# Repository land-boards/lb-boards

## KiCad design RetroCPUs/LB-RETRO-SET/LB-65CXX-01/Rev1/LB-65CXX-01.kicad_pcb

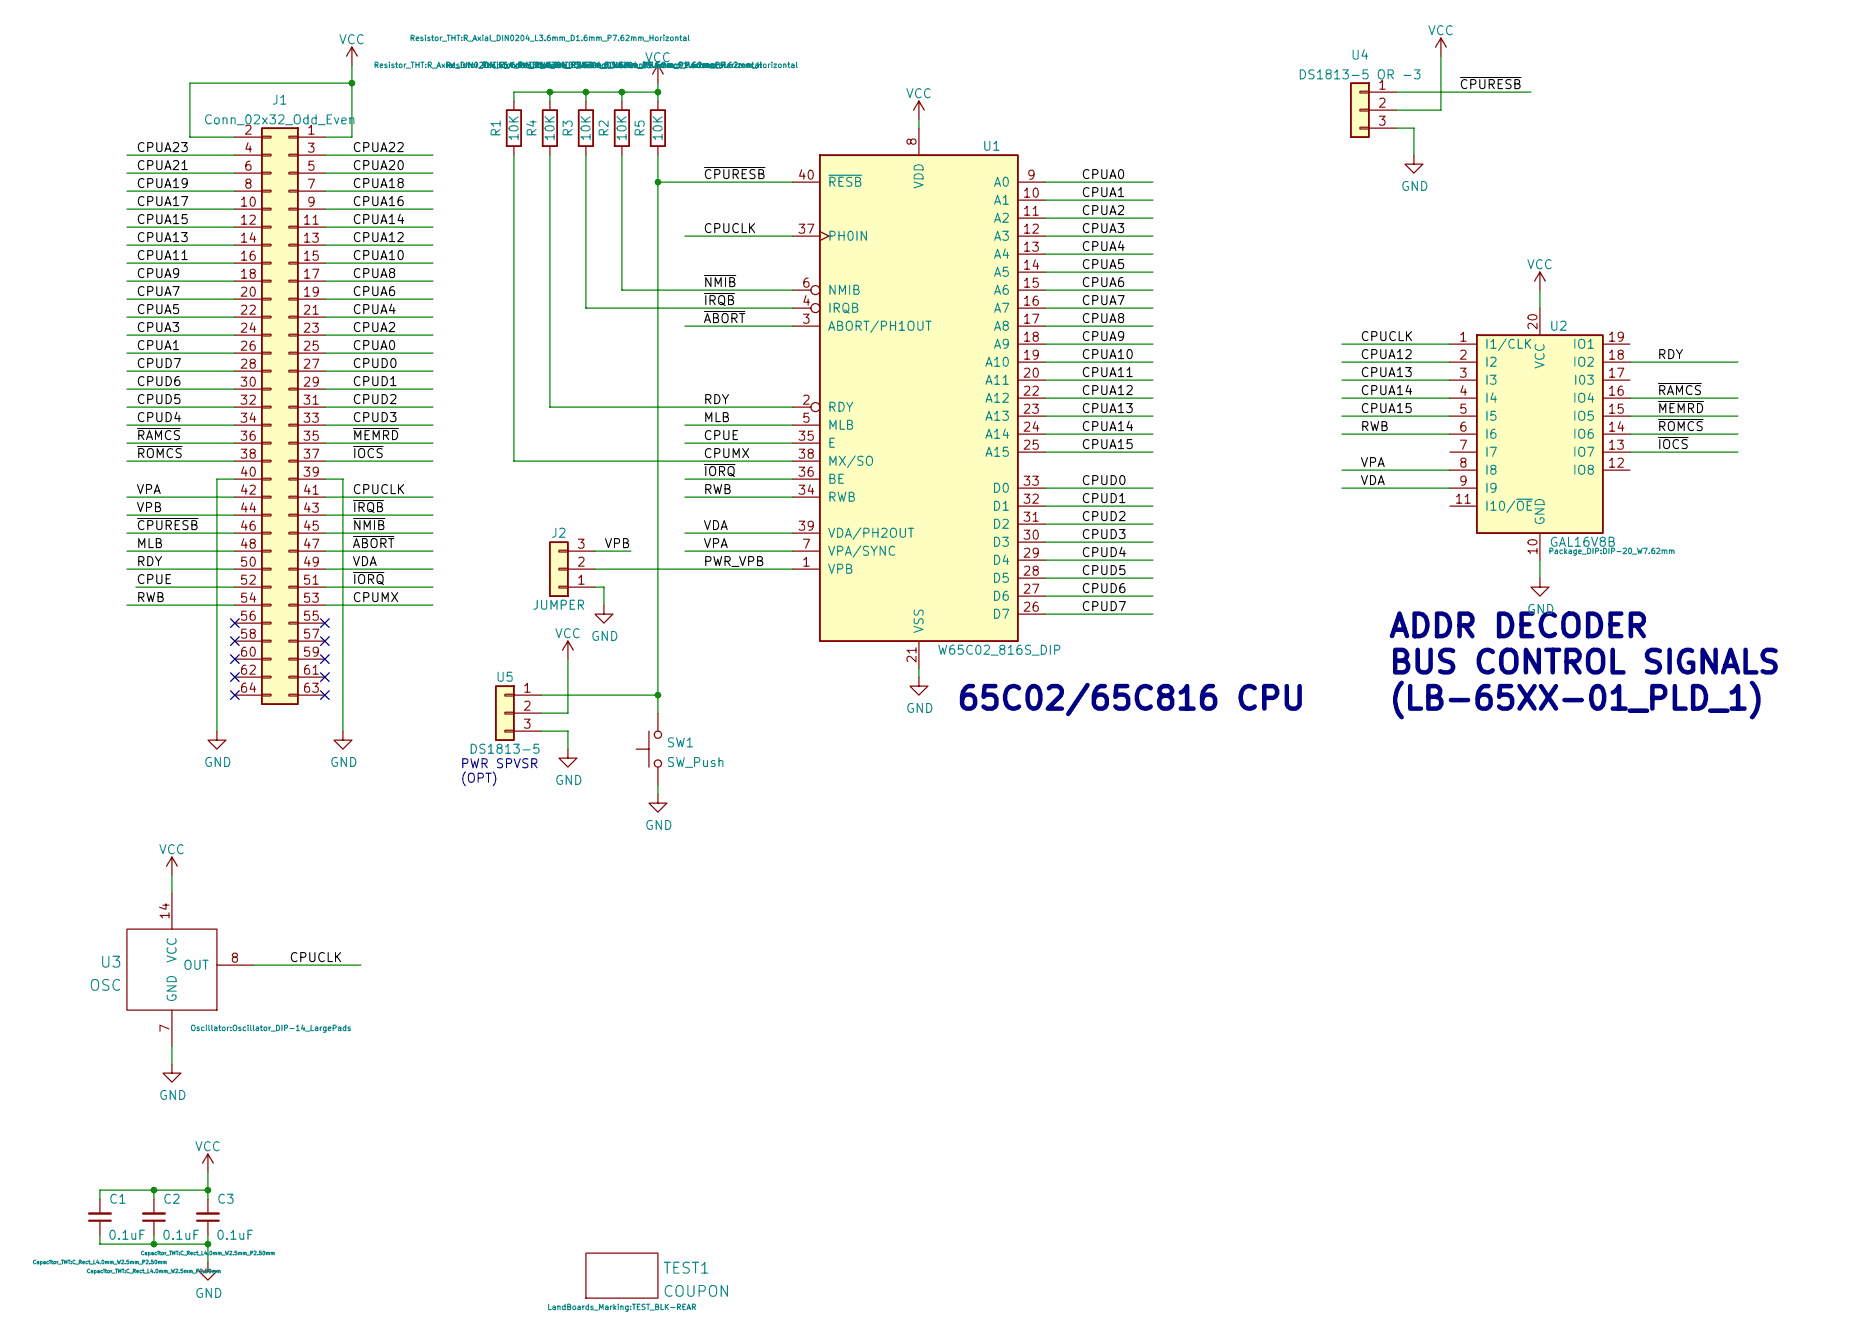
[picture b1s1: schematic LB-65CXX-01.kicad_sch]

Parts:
C1, C2, C3: 0.1uF; C_Rect_L4.0mm_W2.5mm_P2.50mm
J1: Conn_02x32_Odd_Even; PinHeader_2x32_P2.54mm_Horizontal-FLIPPED
J2: JUMPER; PinHeader_1x03_P2.54mm_Vertical
R1, R2, R3, R4, R5: 10K; R_Axial_DIN0204_L3.6mm_D1.6mm_P7.62mm_Horizontal
SW1: SW_Push; SW_PUSH_6mm_H8.5mm
TEST1: COUPON; TEST_BLK-REAR
U1: W65C02_816S_DIP; DIP-40_W15.24mm_LongPads
U2: GAL16V8B; DIP-20_W7.62mm
U3: OSC; Oscillator_DIP-14_LargePads
U4: DS1813-5 OR -3; TO-92
U5: DS1813-5; TO-92

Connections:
/CPUA0: J1.25, U1.9 (A0)
/CPUA1: J1.26, U1.10 (A1)
/CPUA2: J1.23, U1.11 (A2)
/CPUA3: J1.24, U1.12 (A3)
/CPUA4: J1.21, U1.13 (A4)
/CPUA5: J1.22, U1.14 (A5)
/CPUA6: J1.19, U1.15 (A6)
/CPUA7: J1.20, U1.16 (A7)
/CPUA8: J1.17, U1.17 (A8)
/CPUA9: J1.18, U1.18 (A9)
/CPUA10: J1.15, U1.19 (A10)
/CPUA11: J1.16, U1.20 (A11)
/CPUA12: J1.13, U1.22 (A12), U2.2 (I2)
/CPUA13: J1.14, U1.23 (A13), U2.3 (I3)
/CPUA14: J1.11, U1.24 (A14), U2.4 (I4)
/CPUA15: J1.12, U1.25 (A15), U2.5 (I5)
/CPUA16: J1.9
/CPUA17: J1.10
/CPUA18: J1.7
/CPUA19: J1.8
/CPUA20: J1.5
/CPUA21: J1.6
/CPUA22: J1.3
/CPUA23: J1.4
/CPUCLK: J1.41, U1.37 (PH0IN), U2.1 (I1/CLK), U3.8 (OUT)
/CPUD0: J1.27, U1.33 (D0)
/CPUD1: J1.29, U1.32 (D1)
/CPUD2: J1.31, U1.31 (D2)
/CPUD3: J1.33, U1.30 (D3)
/CPUD4: J1.34, U1.29 (D4)
/CPUD5: J1.32, U1.28 (D5)
/CPUD6: J1.30, U1.27 (D6)
/CPUD7: J1.28, U1.26 (D7)
/CPUE: J1.52, U1.35 (E)
/CPUMX: J1.53, R1.2, U1.38 (MX/SO)
/MLB: J1.48, U1.5 (MLB)
/PWR_VPB: J2.2, U1.1 (VPB)
/RDY: J1.50, R4.2, U1.2 (RDY), U2.18 (IO2)
/RWB: J1.54, U1.34 (RWB), U2.6 (I6)
/VDA: J1.49, U1.39 (VDA/PH2OUT), U2.9 (I9)
/VPA: J1.42, U1.7 (VPA/SYNC), U2.8 (I8)
/VPB: J1.44, J2.3
/~ABORT: J1.47, U1.3 (ABORT/PH1OUT)
/~CPURESB: J1.46, R5.2, SW1.2, U1.40 (~RESB), U4.1, U5.1
/~IOCS: J1.37, U2.13 (IO7)
/~IORQ: J1.51, U1.36 (BE)
/~IRQB: J1.43, R3.2, U1.4 (IRQB)
/~MEMRD: J1.35, U2.15 (IO5)
/~NMIB: J1.45, R2.2, U1.6 (NMIB)
/~RAMCS: J1.36, U2.16 (IO4)
/~ROMCS: J1.38, U2.14 (IO6)
GND: C1.1, C2.1, C3.1, J1.39, J1.40, J2.1, SW1.1, U1.21 (VSS), U2.10 (GND), U3.7 (GND), U4.3, U5.3
VCC: C1.2, C2.2, C3.2, J1.1, J1.2, R1.1, R2.1, R3.1, R4.1, R5.1, U1.8 (VDD), U2.20 (VCC), U3.14 (VCC), U4.2, U5.2

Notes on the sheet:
65C02/65C816 CPU
PWR SPVSR (OPT)
ADDR DECODER BUS CONTROL SIGNALS (LB-65XX-01_PLD_1)

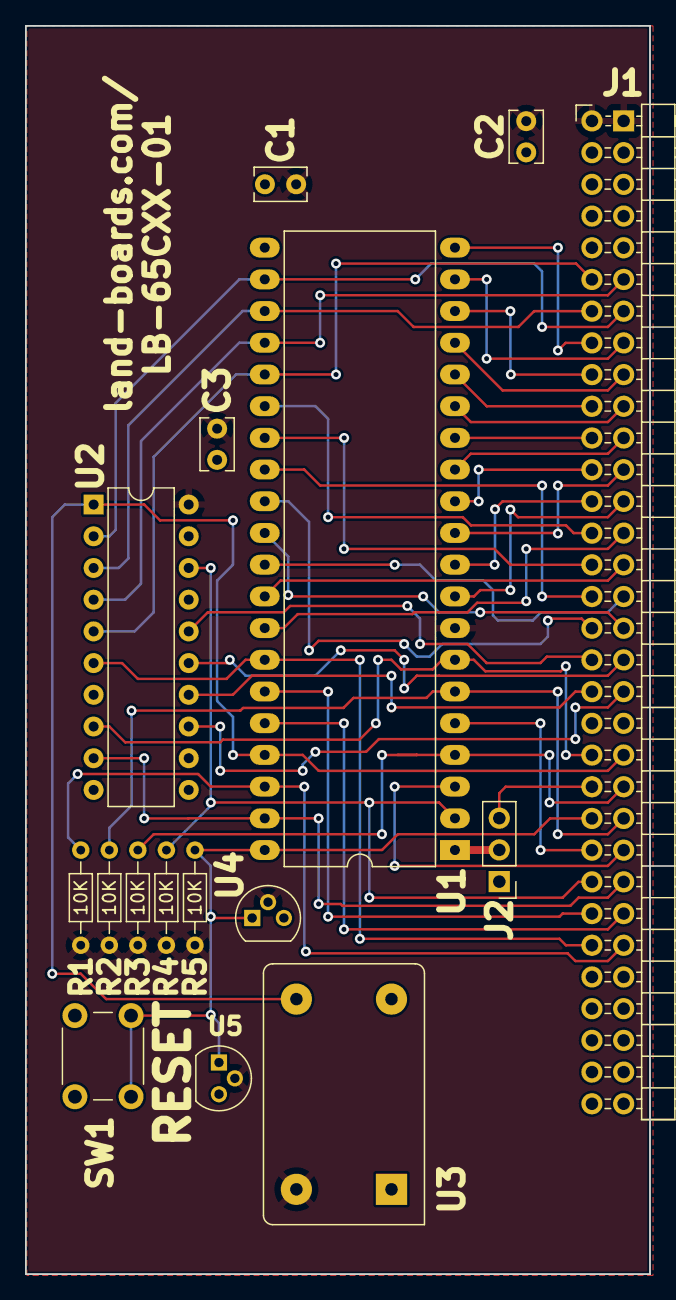
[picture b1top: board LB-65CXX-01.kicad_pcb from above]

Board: 2 copper layers, 50.0 x 100.0 mm, 17 parts (0 on the bottom side), 45 nets.

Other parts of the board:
TEST: COUPON; TEST_BLK-REAR

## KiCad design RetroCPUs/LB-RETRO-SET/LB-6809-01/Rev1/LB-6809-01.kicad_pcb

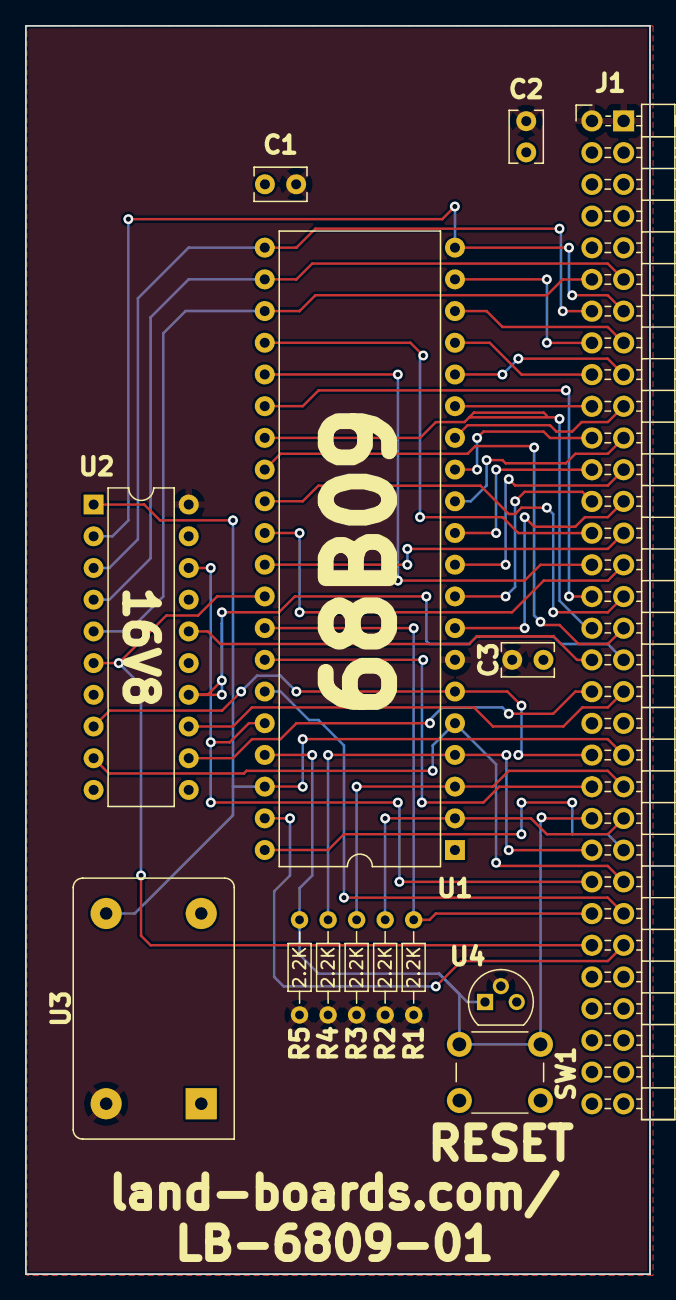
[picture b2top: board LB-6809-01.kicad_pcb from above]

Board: 2 copper layers, 50.0 x 100.0 mm, 15 parts (0 on the bottom side), 44 nets.

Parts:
C1, C2, C3: 0.1uF; C_Rect_L4.0mm_W2.5mm_P2.50mm
J1: Conn_02x32_Odd_Even; PinHeader_2x32_P2.54mm_Horizontal-FLIPPED
R1, R2, R3, R4, R5: 2.2K; R_Axial_DIN0204_L3.6mm_D1.6mm_P7.62mm_Horizontal
SW1: SW_Push; SW_PUSH_6mm_H8.5mm
TEST: COUPON; TEST_BLK-REAR
U1: MC68B09; DIP-40_W15.24mm
U2: GAL16V8; DIP-20_W7.62mm
U3: OSC; Oscillator_DIP-14_LargePads
U4: DS1813-5; TO-92

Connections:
/CPUA0: J1.25, U1.8 (A0)
/CPUA1: J1.26, U1.9 (A1)
/CPUA2: J1.23, U1.10 (A2)
/CPUA3: J1.24, U1.11 (A3)
/CPUA4: J1.21, U1.12 (A4)
/CPUA5: J1.22, U1.13 (A5)
/CPUA6: J1.19, U1.14 (A6)
/CPUA7: J1.20, U1.15 (A7)
/CPUA8: J1.17, U1.16 (A8)
/CPUA9: J1.18, U1.17 (A9)
/CPUA10: J1.15, U1.18 (A10)
/CPUA11: J1.16, U1.19 (A11)
/CPUA12: J1.13, U1.20 (A12), U2.2 (I2)
/CPUA13: J1.14, U1.21 (A13), U2.3 (I3)
/CPUA14: J1.11, U1.22 (A14), U2.4 (I4)
/CPUA15: J1.12, U1.23 (A15), U2.5 (I5)
/CPUCLK: J1.41, U1.38 (EXTAL), U2.1 (I1/CLK), U3.8 (OUT)
/CPUD0: J1.27, U1.31 (D0)
/CPUD1: J1.29, U1.30 (D1)
/CPUD2: J1.31, U1.29 (D2)
/CPUD3: J1.33, U1.28 (D3)
/CPUD4: J1.34, U1.27 (D4)
/CPUD5: J1.32, U1.26 (D5)
/CPUD6: J1.30, U1.25 (D6)
/CPUD7: J1.28, U1.24 (D7)
/CPUE: J1.52, R1.2, U1.33 (~DMA/BREQ)
/CPUMX: J1.53, U1.39 (XTAL)
/MLB: J1.48, R4.2, U1.4 (~FIRQ)
/RDY: J1.50, U1.36 (MRDY), U2.18 (IO2)
/RWB: J1.54, U1.32 (R/~W), U2.6 (I6)
/VDA: J1.49, U1.5 (BS), U2.9 (I9)
/VPA: J1.42, U1.6 (BA), U2.8 (I8)
/VPB: J1.44, U1.34 (E)
/~ABORT: J1.47, U1.40 (~HALT)
/~CPURESB: J1.46, R5.2, SW1.2, U1.37 (~RESET), U4.1
/~IOCS: J1.37, U2.13 (IO7)
/~IORQ: J1.51, U1.35 (Q)
/~IRQB: J1.43, R3.2, U1.3 (~IRQ)
/~MEMRD: J1.35, U2.14 (IO6)
/~NMIB: J1.45, R2.2, U1.2 (~NMI)
/~RAMCS: J1.36, U2.16 (IO4)
/~ROMCS: J1.38, U2.12 (IO8)
GND: C1.1, C2.1, C3.1, J1.39, J1.40, SW1.1, U1.1 (VSS), U2.10 (GND), U3.7 (GND), U4.3
VCC: C1.2, C2.2, C3.2, J1.1, J1.2, R1.1, R2.1, R3.1, R4.1, R5.1, U1.7 (VCC), U2.20 (VCC), U3.14 (VCC), U4.2

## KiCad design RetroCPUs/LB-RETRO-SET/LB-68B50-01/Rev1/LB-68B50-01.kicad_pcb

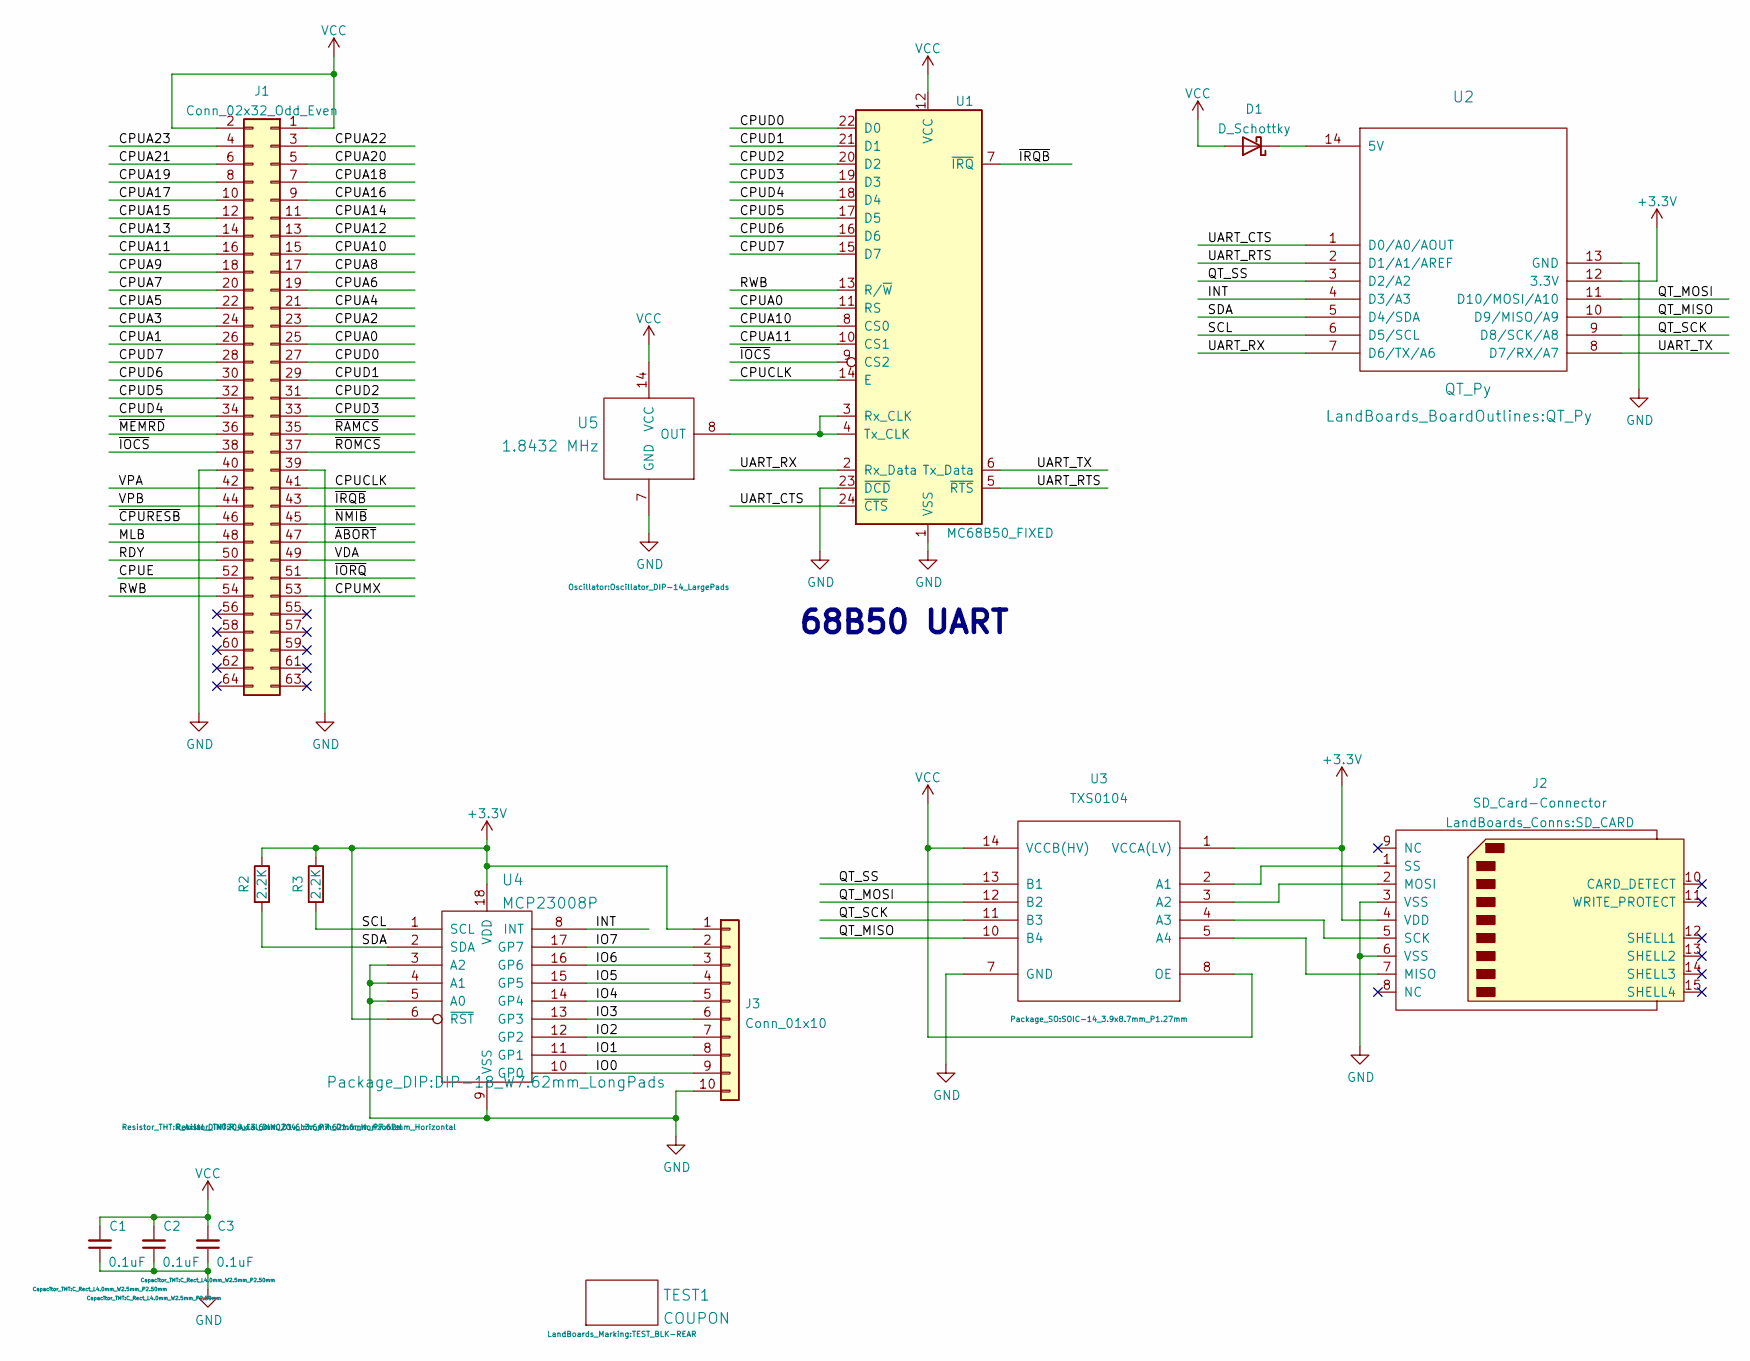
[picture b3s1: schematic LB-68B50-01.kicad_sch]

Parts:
C1, C2, C3: 0.1uF; C_Rect_L4.0mm_W2.5mm_P2.50mm
D1: D_Schottky; D_DO-35_SOD27_P10.16mm_Horizontal
J1: Conn_02x32_Odd_Even; PinHeader_2x32_P2.54mm_Horizontal-FLIPPED
J2: SD_Card-Connector; SD_CARD
J3: Conn_01x10; PinHeader_1x10_P2.54mm_Horizontal
R2, R3: 2.2K; R_Axial_DIN0204_L3.6mm_D1.6mm_P7.62mm_Horizontal
TEST1: COUPON; TEST_BLK-REAR
U1: MC68B50_FIXED; DIP-24_W15.24mm_LongPads
U2: QT_Py
U3: TXS0104; SOIC-14_3.9x8.7mm_P1.27mm
U4: MCP23008P; DIP-18_W7.62mm_LongPads
U5: 1.8432 MHz; Oscillator_DIP-14_LargePads

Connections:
+3V3: J2.4 (VDD), J3.1, R2.1, R3.1, U2.12 (3.3V), U3.1 (VCCA(LV)), U4.6 (~RST), U4.18 (VDD)
/CPUA0: J1.25, U1.11 (RS)
/CPUA1: J1.26
/CPUA2: J1.23
/CPUA3: J1.24
/CPUA4: J1.21
/CPUA5: J1.22
/CPUA6: J1.19
/CPUA7: J1.20
/CPUA8: J1.17
/CPUA9: J1.18
/CPUA10: J1.15, U1.8 (CS0)
/CPUA11: J1.16, U1.10 (CS1)
/CPUA12: J1.13
/CPUA13: J1.14
/CPUA14: J1.11
/CPUA15: J1.12
/CPUA16: J1.9
/CPUA17: J1.10
/CPUA18: J1.7
/CPUA19: J1.8
/CPUA20: J1.5
/CPUA21: J1.6
/CPUA22: J1.3
/CPUA23: J1.4
/CPUCLK: J1.41, U1.14 (E)
/CPUD0: J1.27, U1.22 (D0)
/CPUD1: J1.29, U1.21 (D1)
/CPUD2: J1.31, U1.20 (D2)
/CPUD3: J1.33, U1.19 (D3)
/CPUD4: J1.34, U1.18 (D4)
/CPUD5: J1.32, U1.17 (D5)
/CPUD6: J1.30, U1.16 (D6)
/CPUD7: J1.28, U1.15 (D7)
/CPUE: J1.52
/CPUMX: J1.53
/INT: U2.4 (D3/A3), U4.8 (INT)
/IO0: J3.9, U4.10 (GP0)
/IO1: J3.8, U4.11 (GP1)
/IO2: J3.7, U4.12 (GP2)
/IO3: J3.6, U4.13 (GP3)
/IO4: J3.5, U4.14 (GP4)
/IO5: J3.4, U4.15 (GP5)
/IO6: J3.3, U4.16 (GP6)
/IO7: J3.2, U4.17 (GP7)
/MLB: J1.48
/QT_MISO: U2.10 (D9/MISO/A9), U3.10 (B4)
/QT_MOSI: U2.11 (D10/MOSI/A10), U3.12 (B2)
/QT_SCK: U2.9 (D8/SCK/A8), U3.11 (B3)
/QT_SS: U2.3 (D2/A2), U3.13 (B1)
/RDY: J1.50
/RWB: J1.54, U1.13 (R/~W)
/SCL: R3.2, U2.6 (D5/SCL), U4.1 (SCL)
/SDA: R2.2, U2.5 (D4/SDA), U4.2 (SDA)
/UART_CTS: U1.24 (~CTS), U2.1 (D0/A0/AOUT)
/UART_RTS: U1.5 (~RTS), U2.2 (D1/A1/AREF)
/UART_RX: U1.2 (Rx_Data), U2.7 (D6/TX/A6)
/UART_TX: U1.6 (Tx_Data), U2.8 (D7/RX/A7)
/VDA: J1.49
/VPA: J1.42
/VPB: J1.44
/~ABORT: J1.47
/~CPURESB: J1.46
/~IOCS: J1.38, U1.9 (CS2)
/~IORQ: J1.51
/~IRQB: J1.43, U1.7 (~IRQ)
/~MEMRD: J1.36
/~NMIB: J1.45
/~RAMCS: J1.35
/~ROMCS: J1.37
GND: C1.1, C2.1, C3.1, J1.39, J1.40, J2.3 (VSS), J2.6 (VSS), J3.10, U1.1 (VSS), U1.23 (~DCD), U2.13 (GND), U3.7 (GND), U4.3 (A2), U4.4 (A1), U4.5 (A0), U4.9 (VSS), U5.7 (GND)
unnamed: J2.1 (SS), U3.2 (A1)
unnamed: J2.2 (MOSI), U3.3 (A2)
unnamed: J2.5 (SCK), U3.4 (A3)
unnamed: J2.7 (MISO), U3.5 (A4)
unnamed: U1.3 (Rx_CLK), U1.4 (Tx_CLK), U5.8 (OUT)
unnamed: D1.1 (K), U2.14 (5V)
VCC: C1.2, C2.2, C3.2, D1.2 (A), J1.1, J1.2, U1.12 (VCC), U3.8 (OE), U3.14 (VCCB(HV)), U5.14 (VCC)

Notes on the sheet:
68B50 UART

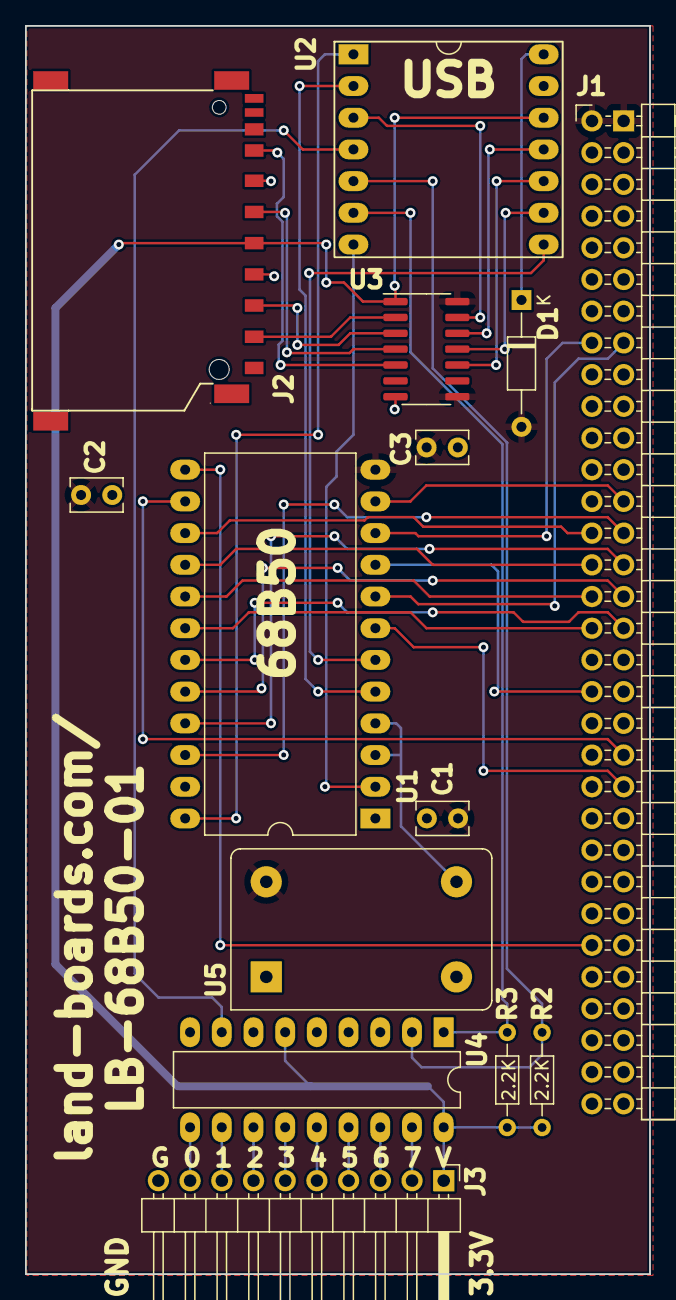
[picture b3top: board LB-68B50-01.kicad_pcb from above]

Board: 2 copper layers, 50.0 x 100.0 mm, 15 parts (0 on the bottom side), 43 nets.

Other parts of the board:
TEST: COUPON; TEST_BLK-REAR

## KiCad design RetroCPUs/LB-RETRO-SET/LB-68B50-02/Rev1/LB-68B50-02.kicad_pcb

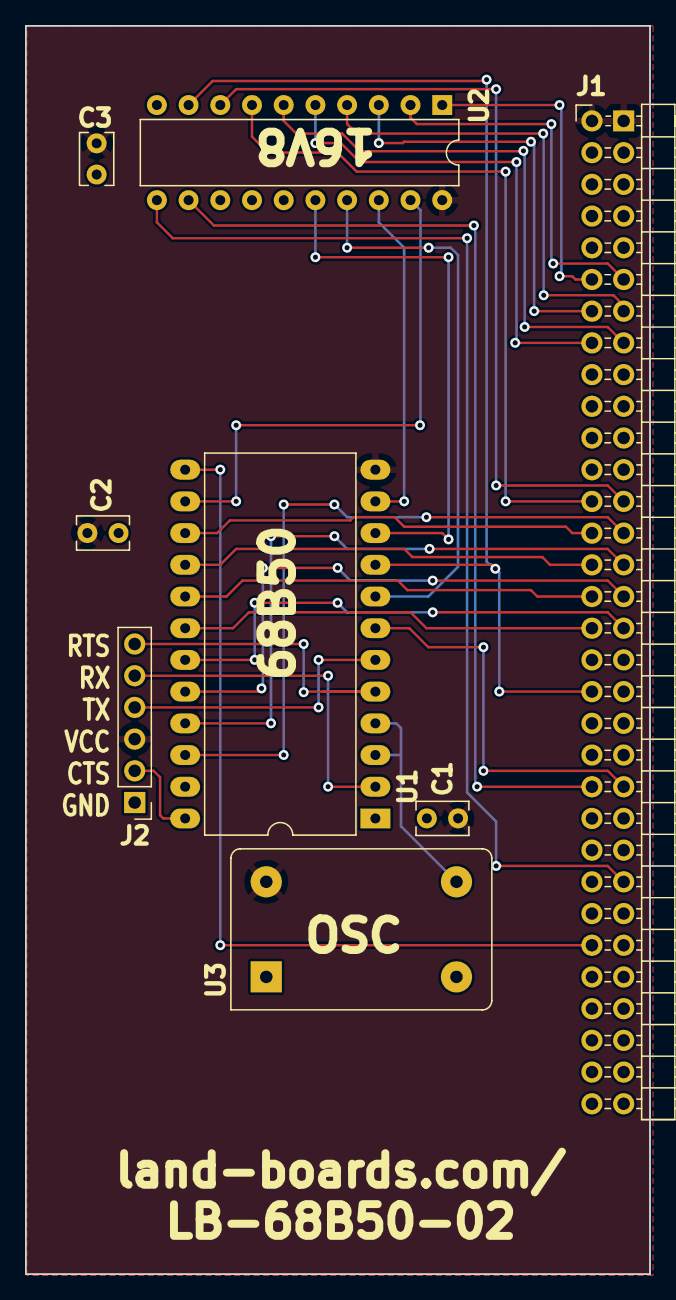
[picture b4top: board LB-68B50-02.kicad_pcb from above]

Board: 2 copper layers, 50.0 x 100.0 mm, 9 parts (0 on the bottom side), 32 nets.

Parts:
C1, C2, C3: 0.1uF; C_Rect_L4.0mm_W2.5mm_P2.50mm
J1: Conn_2x32_RtAng; PinHeader_2x32_P2.54mm_Horizontal-FLIPPED
J2: 1x6_Pin_Header_Rt_Angle; PinHeader_1x06_P2.54mm_Vertical
TEST: COUPON; TEST_BLK-REAR
U1: MC68B50; DIP-24_W15.24mm_LongPads
U2: ATF16V8B-15PU; DIP-20_W7.62mm
U3: MXO45-3C-1M8432; Oscillator_DIP-14_LargePads

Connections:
/ACIACS0: U1.8 (CS0), U2.17 (I03)
/ACIACS1: U1.10 (CS1), U2.16 (IO4)
/ACIAE: U1.14 (E), U2.19 (IO1)
/ACIARS: U1.11 (RS), U2.18 (IO2)
/CPUA0: J1.25, U2.8 (I8)
/CPUA1: J1.26, U2.7 (I7)
/CPUA10: J1.15, U2.6 (I6)
/CPUA11: J1.16, U2.5 (I5)
/CPUA12: J1.13, U2.4 (I4)
/CPUA13: J1.14, U2.3 (I3)
/CPUA14: J1.11, U2.2 (I2)
/CPUA15: J1.12, U2.1 (I1/CLK)
/CPUD0: J1.27, U1.22 (D0)
/CPUD1: J1.29, U1.21 (D1)
/CPUD2: J1.31, U1.20 (D2)
/CPUD3: J1.33, U1.19 (D3)
/CPUD4: J1.34, U1.18 (D4)
/CPUD5: J1.32, U1.17 (D5)
/CPUD6: J1.30, U1.16 (D6)
/CPUD7: J1.28, U1.15 (D7)
/RWB: J1.54, U1.13 (R/~W)
/UART_CTS_5: J2.2 (<CTS), U1.24 (~CTS)
/UART_RTS_5: J2.6 (RTS>), U1.5 (~RTS)
/UART_RX_5: J2.5 (RX<), U1.2 (Rx_Data)
/UART_TX_5: J2.4 (TX>), U1.6 (Tx_Data)
/VDA: J1.49, U2.11 (I10/~OE)
/VPB: J1.44, U2.12 (IO8)
/~IOCS: J1.38, U1.9 (CS2), U2.9 (I9)
/~IRQB: J1.43, U1.7 (~IRQ)
GND: C1.1, C2.1, C3.1, J1.39, J1.40, J2.1 (GND), U1.1 (VSS), U1.23 (~DCD), U2.10 (GND), U3.7 (GND)
unnamed: U1.3 (Rx_CLK), U1.4 (Tx_CLK), U3.8 (OUT)
VCC: C1.2, C2.2, C3.2, J1.1, J1.2, J2.3 (VCC), U1.12 (VCC), U2.20 (VCC), U3.14 (VCC)

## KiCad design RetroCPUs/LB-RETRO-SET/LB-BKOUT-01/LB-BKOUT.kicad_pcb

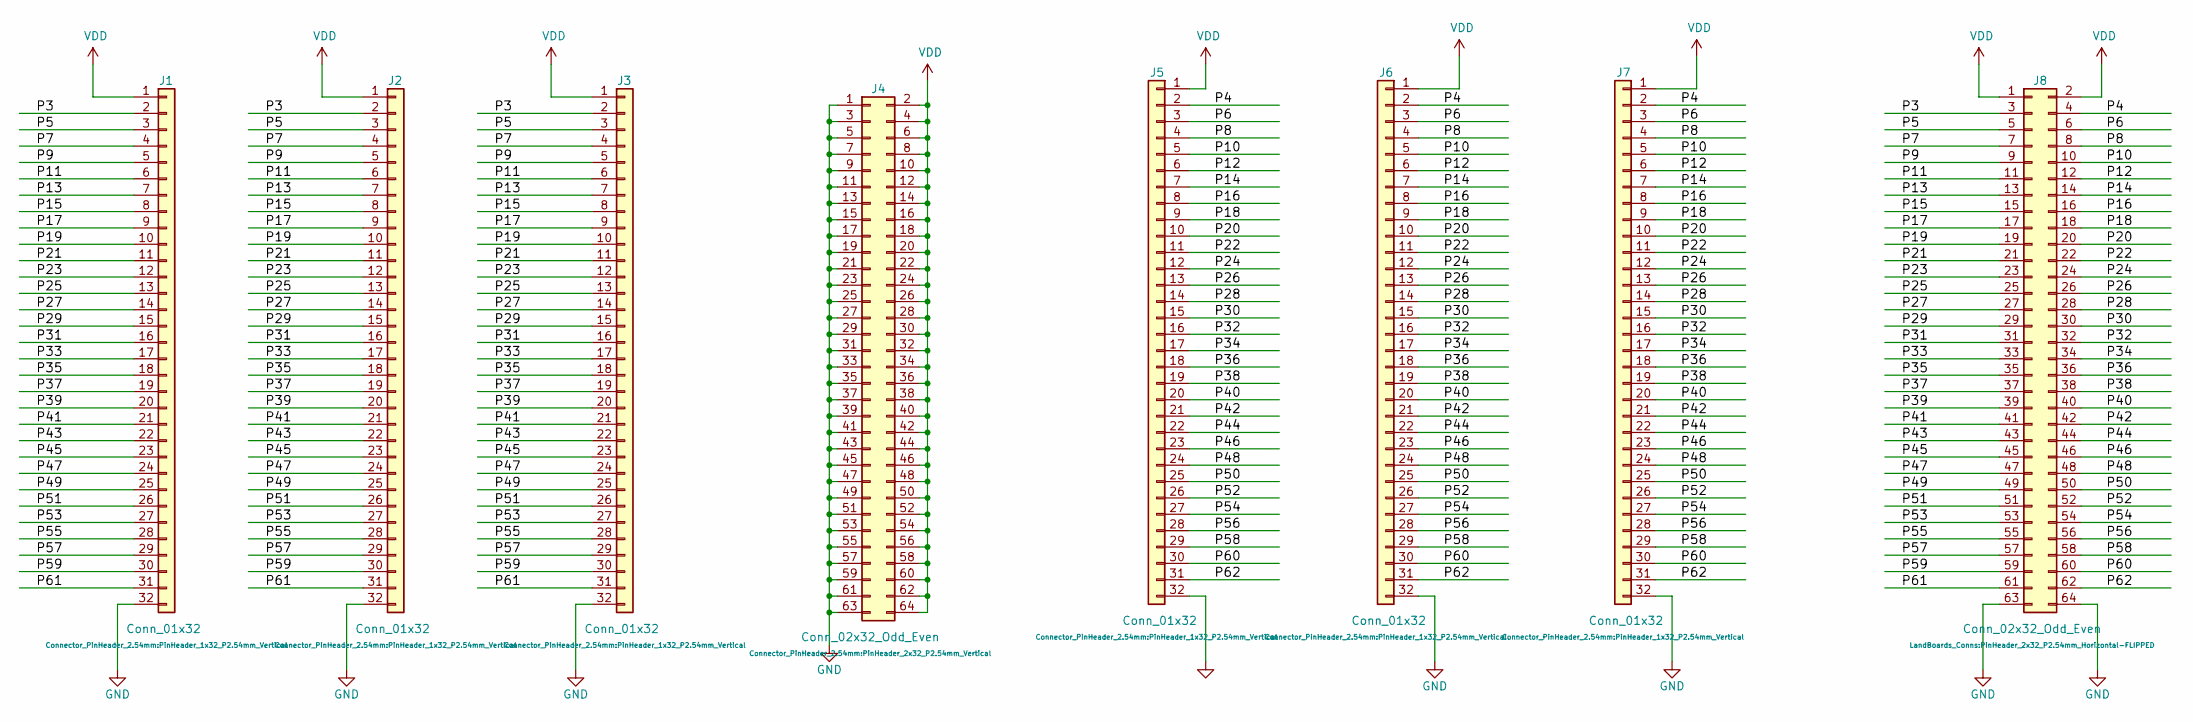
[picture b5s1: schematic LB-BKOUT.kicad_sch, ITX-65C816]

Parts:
J1, J2, J3, J5, J6, J7: Conn_01x32; PinHeader_1x32_P2.54mm_Vertical
J4: Conn_02x32_Odd_Even; PinHeader_2x32_P2.54mm_Vertical
J8: Conn_02x32_Odd_Even; PinHeader_2x32_P2.54mm_Horizontal-FLIPPED

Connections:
/P3: J1.2, J2.2, J3.2, J8.3
/P4: J5.2, J6.2, J7.2, J8.4
/P5: J1.3, J2.3, J3.3, J8.5
/P6: J5.3, J6.3, J7.3, J8.6
/P7: J1.4, J2.4, J3.4, J8.7
/P8: J5.4, J6.4, J7.4, J8.8
/P9: J1.5, J2.5, J3.5, J8.9
/P10: J5.5, J6.5, J7.5, J8.10
/P11: J1.6, J2.6, J3.6, J8.11
/P12: J5.6, J6.6, J7.6, J8.12
/P13: J1.7, J2.7, J3.7, J8.13
/P14: J5.7, J6.7, J7.7, J8.14
/P15: J1.8, J2.8, J3.8, J8.15
/P16: J5.8, J6.8, J7.8, J8.16
/P17: J1.9, J2.9, J3.9, J8.17
/P18: J5.9, J6.9, J7.9, J8.18
/P19: J1.10, J2.10, J3.10, J8.19
/P20: J5.10, J6.10, J7.10, J8.20
/P21: J1.11, J2.11, J3.11, J8.21
/P22: J5.11, J6.11, J7.11, J8.22
/P23: J1.12, J2.12, J3.12, J8.23
/P24: J5.12, J6.12, J7.12, J8.24
/P25: J1.13, J2.13, J3.13, J8.25
/P26: J5.13, J6.13, J7.13, J8.26
/P27: J1.14, J2.14, J3.14, J8.27
/P28: J5.14, J6.14, J7.14, J8.28
/P29: J1.15, J2.15, J3.15, J8.29
/P30: J5.15, J6.15, J7.15, J8.30
/P31: J1.16, J2.16, J3.16, J8.31
/P32: J5.16, J6.16, J7.16, J8.32
/P33: J1.17, J2.17, J3.17, J8.33
/P34: J5.17, J6.17, J7.17, J8.34
/P35: J1.18, J2.18, J3.18, J8.35
/P36: J5.18, J6.18, J7.18, J8.36
/P37: J1.19, J2.19, J3.19, J8.37
/P38: J5.19, J6.19, J7.19, J8.38
/P39: J1.20, J2.20, J3.20, J8.39
/P40: J5.20, J6.20, J7.20, J8.40
/P41: J1.21, J2.21, J3.21, J8.41
/P42: J5.21, J6.21, J7.21, J8.42
/P43: J1.22, J2.22, J3.22, J8.43
/P44: J5.22, J6.22, J7.22, J8.44
/P45: J1.23, J2.23, J3.23, J8.45
/P46: J5.23, J6.23, J7.23, J8.46
/P47: J1.24, J2.24, J3.24, J8.47
/P48: J5.24, J6.24, J7.24, J8.48
/P49: J1.25, J2.25, J3.25, J8.49
/P50: J5.25, J6.25, J7.25, J8.50
/P51: J1.26, J2.26, J3.26, J8.51
/P52: J5.26, J6.26, J7.26, J8.52
/P53: J1.27, J2.27, J3.27, J8.53
/P54: J5.27, J6.27, J7.27, J8.54
/P55: J1.28, J2.28, J3.28, J8.55
/P56: J5.28, J6.28, J7.28, J8.56
/P57: J1.29, J2.29, J3.29, J8.57
/P58: J5.29, J6.29, J7.29, J8.58
/P59: J1.30, J2.30, J3.30, J8.59
/P60: J5.30, J6.30, J7.30, J8.60
/P61: J1.31, J2.31, J3.31, J8.61
/P62: J5.31, J6.31, J7.31, J8.62
GND: J1.32, J2.32, J3.32, J4.1, J4.3, J4.5, J4.7, J4.9, J4.11, J4.13, J4.15, J4.17, J4.19, J4.21, J4.23, J4.25, J4.27, J4.29, J4.31, J4.33, J4.35, J4.37, J4.39, J4.41, J4.43, J4.45, J4.47, J4.49, J4.51, J4.53, J4.55, J4.57, J4.59, J4.61, J4.63, J5.32, J6.32, J7.32, J8.63, J8.64
VDD: J1.1, J2.1, J3.1, J4.2, J4.4, J4.6, J4.8, J4.10, J4.12, J4.14, J4.16, J4.18, J4.20, J4.22, J4.24, J4.26, J4.28, J4.30, J4.32, J4.34, J4.36, J4.38, J4.40, J4.42, J4.44, J4.46, J4.48, J4.50, J4.52, J4.54, J4.56, J4.58, J4.60, J4.62, J4.64, J5.1, J6.1, J7.1, J8.1, J8.2

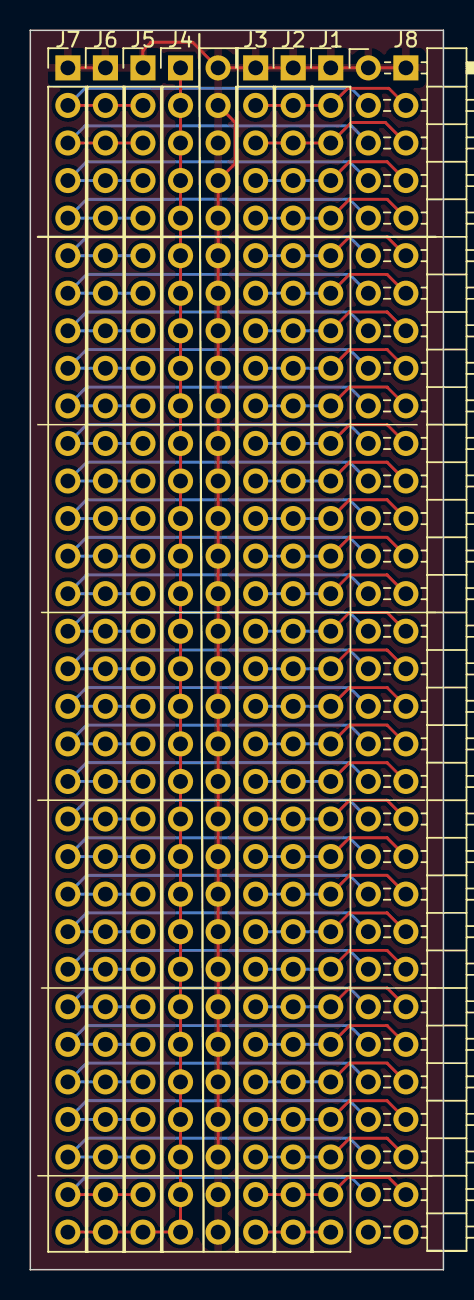
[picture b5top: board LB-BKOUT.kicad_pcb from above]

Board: 2 copper layers, 27.9 x 83.8 mm, 8 parts (0 on the bottom side), 62 nets.

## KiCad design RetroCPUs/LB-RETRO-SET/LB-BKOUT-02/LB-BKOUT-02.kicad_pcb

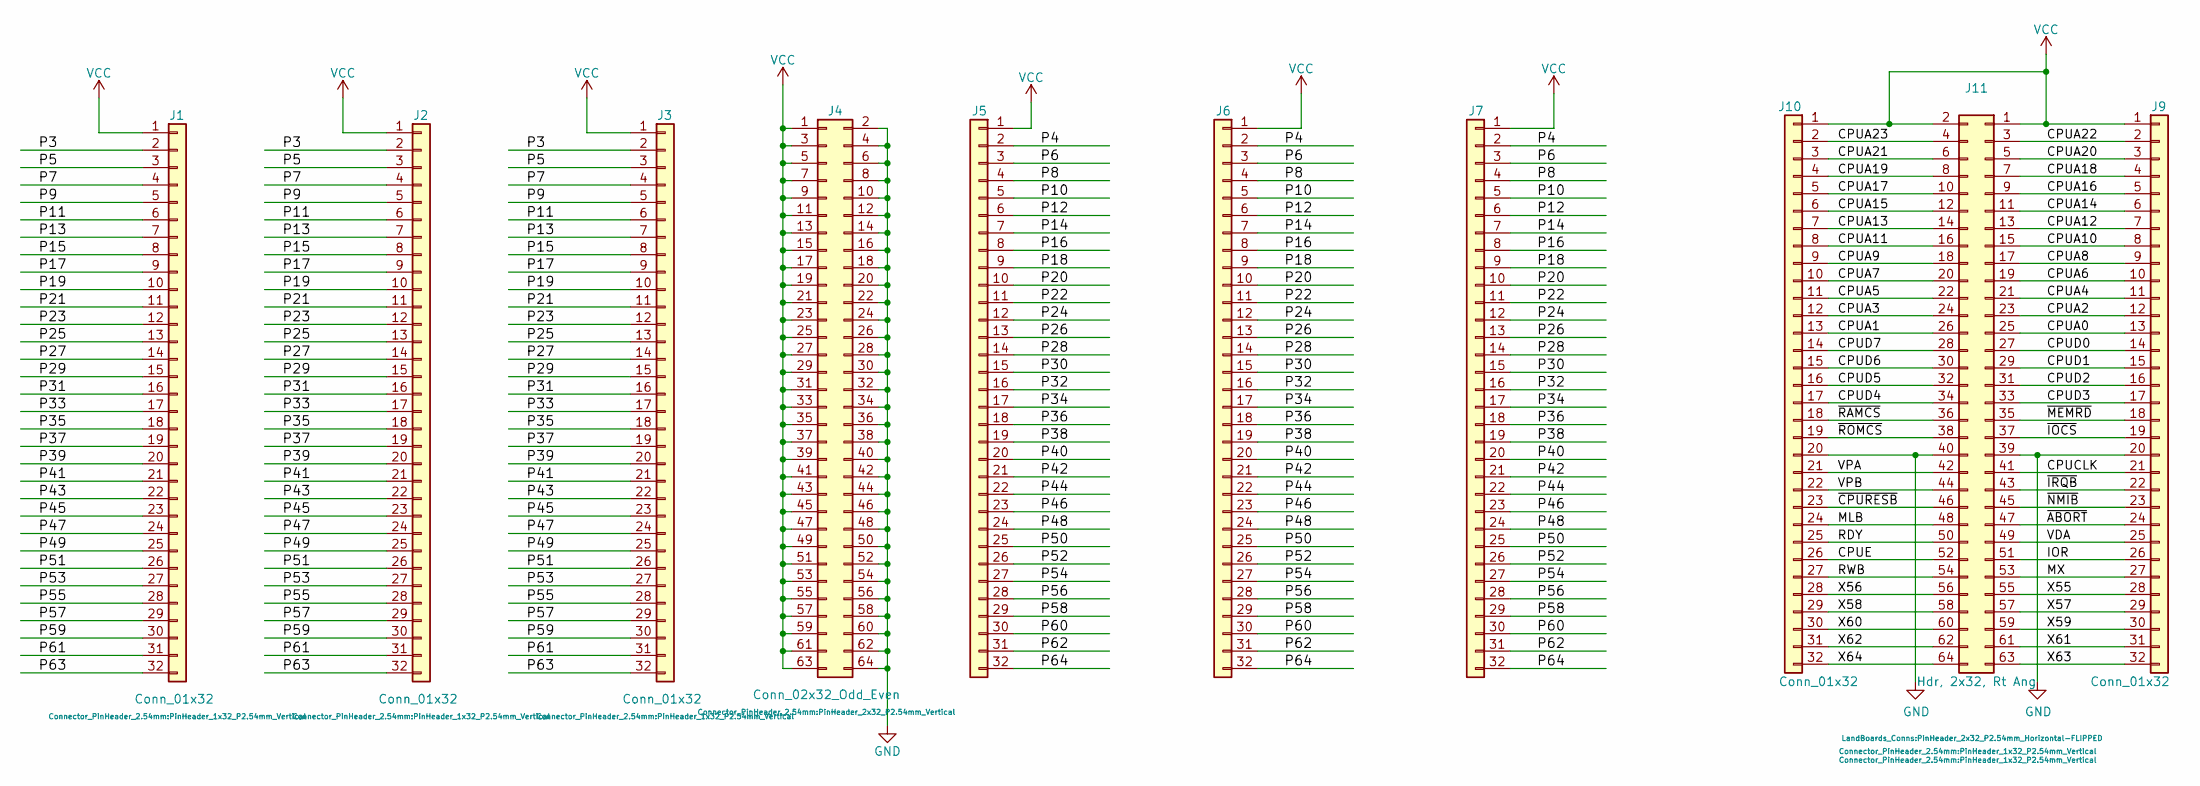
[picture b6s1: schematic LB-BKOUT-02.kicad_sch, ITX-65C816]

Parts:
J1, J2, J3, J5, J6, J7, J9, J10: Conn_01x32; PinHeader_1x32_P2.54mm_Vertical
J4: Conn_02x32_Odd_Even; PinHeader_2x32_P2.54mm_Vertical
J11: Hdr, 2x32, Rt Ang; PinHeader_2x32_P2.54mm_Horizontal-FLIPPED

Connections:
/CPUA0: J9.13, J11.25
/CPUA1: J10.13, J11.26
/CPUA2: J9.12, J11.23
/CPUA3: J10.12, J11.24
/CPUA4: J9.11, J11.21
/CPUA5: J10.11, J11.22
/CPUA6: J9.10, J11.19
/CPUA7: J10.10, J11.20
/CPUA8: J9.9, J11.17
/CPUA9: J10.9, J11.18
/CPUA10: J9.8, J11.15
/CPUA11: J10.8, J11.16
/CPUA12: J9.7, J11.13
/CPUA13: J10.7, J11.14
/CPUA14: J9.6, J11.11
/CPUA15: J10.6, J11.12
/CPUA16: J9.5, J11.9
/CPUA17: J10.5, J11.10
/CPUA18: J9.4, J11.7
/CPUA19: J10.4, J11.8
/CPUA20: J9.3, J11.5
/CPUA21: J10.3, J11.6
/CPUA22: J9.2, J11.3
/CPUA23: J10.2, J11.4
/CPUCLK: J9.21, J11.41
/CPUD0: J9.14, J11.27
/CPUD1: J9.15, J11.29
/CPUD2: J9.16, J11.31
/CPUD3: J9.17, J11.33
/CPUD4: J10.17, J11.34
/CPUD5: J10.16, J11.32
/CPUD6: J10.15, J11.30
/CPUD7: J10.14, J11.28
/CPUE: J10.26, J11.52
/IOR: J9.26, J11.51
/MLB: J10.24, J11.48
/MX: J9.27, J11.53
/P3: J1.2, J2.2, J3.2
/P4: J5.2, J6.2, J7.2
/P5: J1.3, J2.3, J3.3
/P6: J5.3, J6.3, J7.3
/P7: J1.4, J2.4, J3.4
/P8: J5.4, J6.4, J7.4
/P9: J1.5, J2.5, J3.5
/P10: J5.5, J6.5, J7.5
/P11: J1.6, J2.6, J3.6
/P12: J5.6, J6.6, J7.6
/P13: J1.7, J2.7, J3.7
/P14: J5.7, J6.7, J7.7
/P15: J1.8, J2.8, J3.8
/P16: J5.8, J6.8, J7.8
/P17: J1.9, J2.9, J3.9
/P18: J5.9, J6.9, J7.9
/P19: J1.10, J2.10, J3.10
/P20: J5.10, J6.10, J7.10
/P21: J1.11, J2.11, J3.11
/P22: J5.11, J6.11, J7.11
/P23: J1.12, J2.12, J3.12
/P24: J5.12, J6.12, J7.12
/P25: J1.13, J2.13, J3.13
/P26: J5.13, J6.13, J7.13
/P27: J1.14, J2.14, J3.14
/P28: J5.14, J6.14, J7.14
/P29: J1.15, J2.15, J3.15
/P30: J5.15, J6.15, J7.15
/P31: J1.16, J2.16, J3.16
/P32: J5.16, J6.16, J7.16
/P33: J1.17, J2.17, J3.17
/P34: J5.17, J6.17, J7.17
/P35: J1.18, J2.18, J3.18
/P36: J5.18, J6.18, J7.18
/P37: J1.19, J2.19, J3.19
/P38: J5.19, J6.19, J7.19
/P39: J1.20, J2.20, J3.20
/P40: J5.20, J6.20, J7.20
/P41: J1.21, J2.21, J3.21
/P42: J5.21, J6.21, J7.21
/P43: J1.22, J2.22, J3.22
/P44: J5.22, J6.22, J7.22
/P45: J1.23, J2.23, J3.23
/P46: J5.23, J6.23, J7.23
/P47: J1.24, J2.24, J3.24
/P48: J5.24, J6.24, J7.24
/P49: J1.25, J2.25, J3.25
/P50: J5.25, J6.25, J7.25
/P51: J1.26, J2.26, J3.26
/P52: J5.26, J6.26, J7.26
/P53: J1.27, J2.27, J3.27
/P54: J5.27, J6.27, J7.27
/P55: J1.28, J2.28, J3.28
/P56: J5.28, J6.28, J7.28
/P57: J1.29, J2.29, J3.29
/P58: J5.29, J6.29, J7.29
/P59: J1.30, J2.30, J3.30
/P60: J5.30, J6.30, J7.30
/P61: J1.31, J2.31, J3.31
/P62: J5.31, J6.31, J7.31
/P63: J1.32, J2.32, J3.32
/P64: J5.32, J6.32, J7.32
/RDY: J10.25, J11.50
/RWB: J10.27, J11.54
/VDA: J9.25, J11.49
/VPA: J10.21, J11.42
/VPB: J10.22, J11.44
/X55: J9.28, J11.55
/X56: J10.28, J11.56
/X57: J9.29, J11.57
/X58: J10.29, J11.58
/X59: J9.30, J11.59
/X60: J10.30, J11.60
/X61: J9.31, J11.61
/X62: J10.31, J11.62
/X63: J9.32, J11.63
/X64: J10.32, J11.64
/~ABORT: J9.24, J11.47
/~CPURESB: J10.23, J11.46
/~IOCS: J9.19, J11.37
/~IRQB: J9.22, J11.43
/~MEMRD: J9.18, J11.35
/~NMIB: J9.23, J11.45
/~RAMCS: J10.18, J11.36
/~ROMCS: J10.19, J11.38
GND: J4.2, J4.4, J4.6, J4.8, J4.10, J4.12, J4.14, J4.16, J4.18, J4.20, J4.22, J4.24, J4.26, J4.28, J4.30, J4.32, J4.34, J4.36, J4.38, J4.40, J4.42, J4.44, J4.46, J4.48, J4.50, J4.52, J4.54, J4.56, J4.58, J4.60, J4.62, J4.64, J9.20, J10.20, J11.39, J11.40
VCC: J1.1, J2.1, J3.1, J4.1, J4.3, J4.5, J4.7, J4.9, J4.11, J4.13, J4.15, J4.17, J4.19, J4.21, J4.23, J4.25, J4.27, J4.29, J4.31, J4.33, J4.35, J4.37, J4.39, J4.41, J4.43, J4.45, J4.47, J4.49, J4.51, J4.53, J4.55, J4.57, J4.59, J4.61, J4.63, J5.1, J6.1, J7.1, J9.1, J10.1, J11.1, J11.2

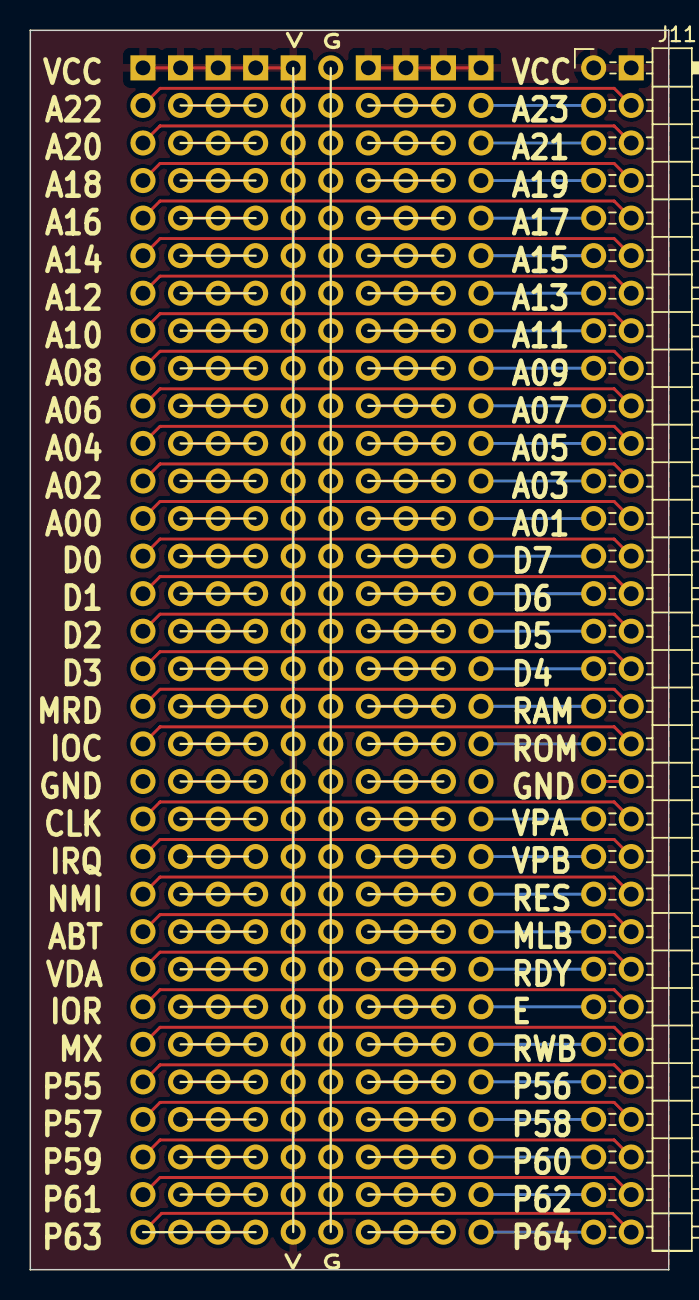
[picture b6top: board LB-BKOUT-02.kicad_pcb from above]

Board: 2 copper layers, 43.2 x 83.8 mm, 10 parts (0 on the bottom side), 124 nets.
